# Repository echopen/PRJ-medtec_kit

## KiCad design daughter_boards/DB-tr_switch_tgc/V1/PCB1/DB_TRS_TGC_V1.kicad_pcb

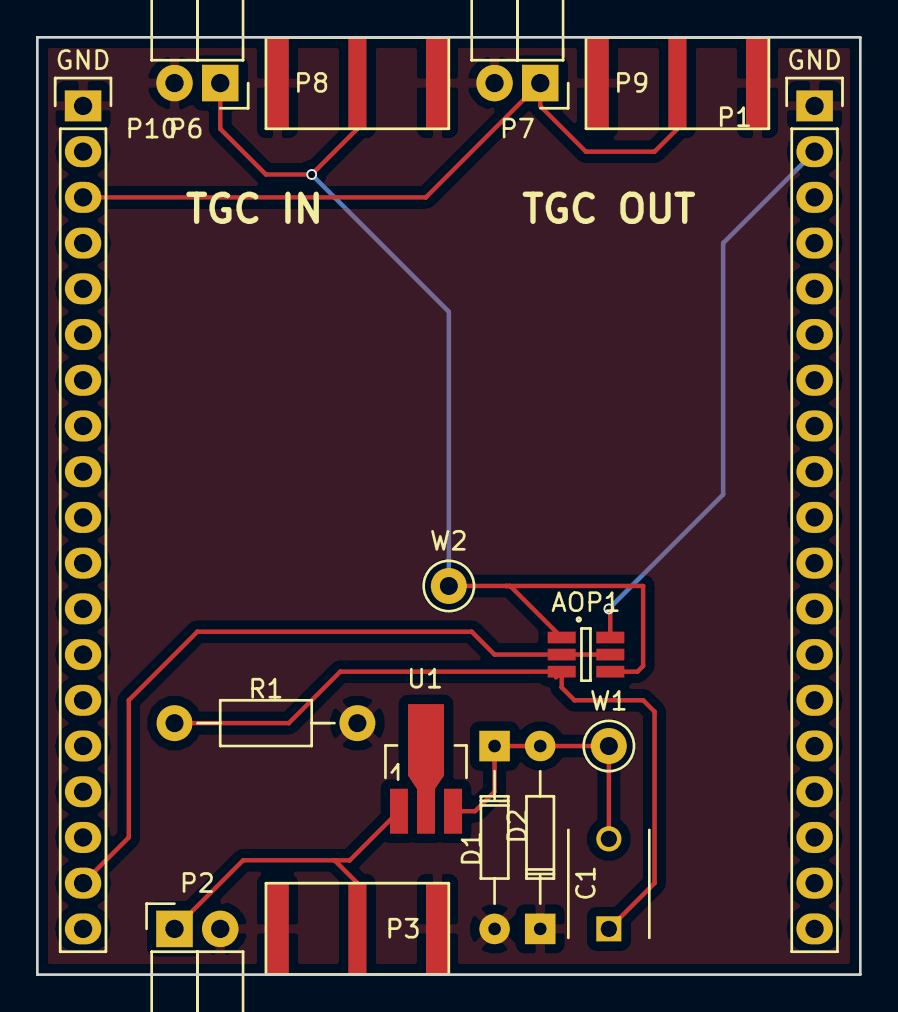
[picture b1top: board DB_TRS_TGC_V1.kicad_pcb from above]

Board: 2 copper layers, 45.7 x 52.1 mm, 16 parts (0 on the bottom side), 8 nets.

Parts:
AOP1: OPA625; SOT-23-6_Handsoldering(OPA625)
C1: 1n; C_TH_common
D1: 1N4148; D_TH_common
D2: IN4148; D_TH_common
P1, P10: CONN_01X19; Header_pin_1x19
P2, P6, P7: CONN_01X02; Socket_Strip_Angled_1x02
P3, P8, P9: SMA
R1: 220; Resistor_TH_common
U1: MD0100; SOT89-3_(MD0100)
W1, W2: TEST_1P; Test_Point_Keystone_5000-5004_Miniature

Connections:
GND: D1.2, D2.1, P1.1, P2.2, P3.2, P6.2, P7.2, P8.2, P9.2, P10.1, R1.2
unnamed: AOP1.1, AOP1.4, P6.1, P8.1, W2.1
unnamed: AOP1.2, AOP1.5, P10.18
unnamed: AOP1.3, C1.1, R1.1
unnamed: AOP1.6, P1.2
unnamed: C1.2, D1.1, D2.2, U1.3, W1.1
unnamed: P2.1, P3.1, U1.1
unnamed: P7.1, P9.1, P10.3

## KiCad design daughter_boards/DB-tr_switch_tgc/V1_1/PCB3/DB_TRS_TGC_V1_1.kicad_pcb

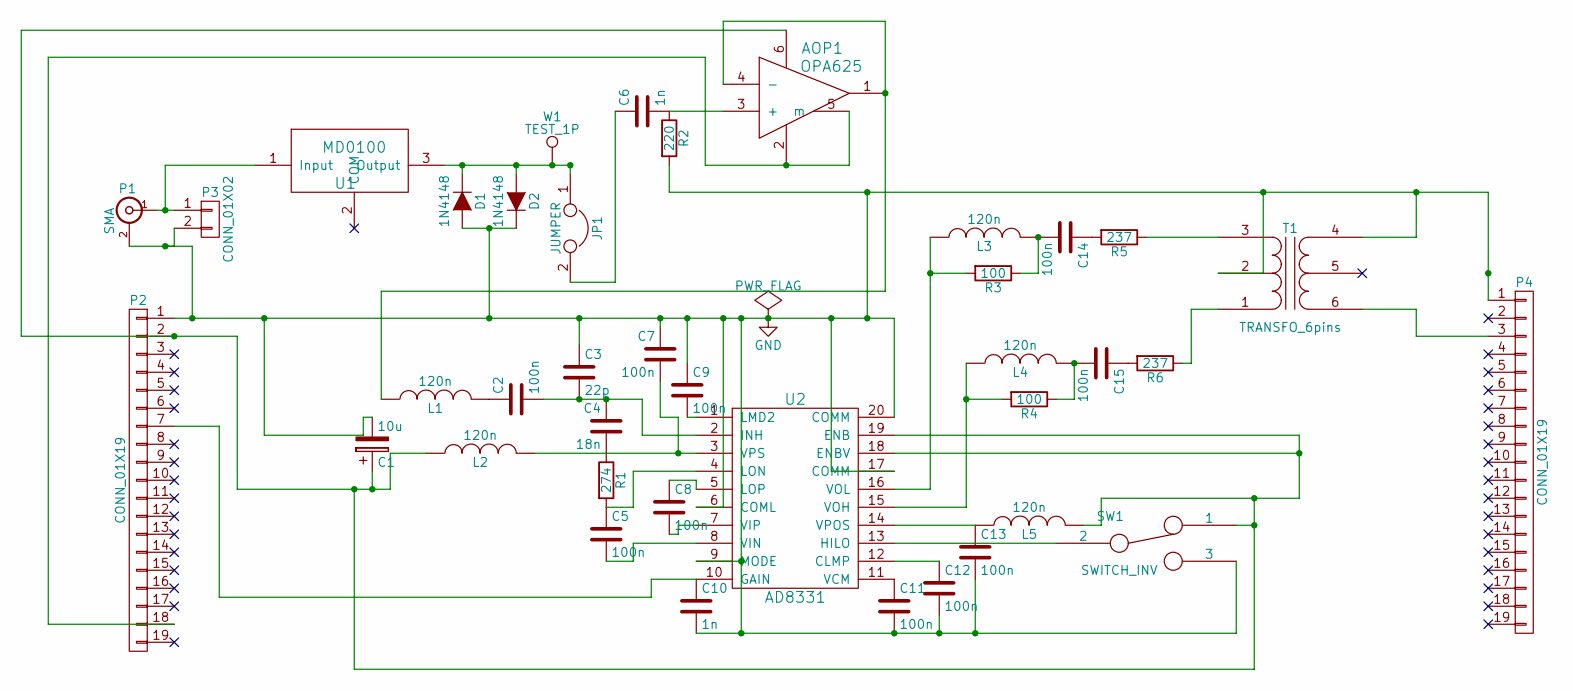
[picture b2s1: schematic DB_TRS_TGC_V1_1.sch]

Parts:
AOP1: OPA625; SOT-23-6_Handsoldering(OPA625)
C1: 10u; CP_TH_common
C2, C5, C7, C8, C9, C11, C12, C13, C14, C15: 100n; C_TH_common
C3: 22p; C_TH_common
C4: 18n; C_TH_common
C6, C10: 1n; C_TH_common
D1, D2: 1N4148; D_TH_common
JP1: JUMPER; Jumper
L1, L2, L3, L4, L5: 120n; INDUCTOR_TH_common
P1: SMA
P2, P4: CONN_01X19; Header_1x19
P3: CONN_01X02; Socket_Strip_Angled_1x02
R1: 274; Resistor_TH_common
R2: 220; Resistor_TH_common
R3, R4: 100; Resistor_TH_common
R5, R6: 237; Resistor_TH_common
SW1: SWITCH_INV; SW_Micro_SPST
T1: TRANSFO_6pins; Transfo_6pins
U1: MD0100; SOT89-3_Housing_Handsoldering
U2: AD8331; SSOP-20_5.3x7.2mm_Pitch0.65mm
W1: TEST_1P; Test_Point_Keystone_5000-5004_Miniature

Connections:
GND: C1.2, C3.1, C7.1, C9.1, C10.2, C11.2, C12.2, C13.2, D1.2 (A), D2.1 (K), P1.2 (Ext), P2.1, P3.2, P4.1, R2.2, SW1.3, T1.2 (PM), T1.4 (S2), U2.6 (COML), U2.9 (MODE), U2.17 (COMM), U2.20 (COMM)
unnamed: AOP1.1, AOP1.4 (-), L1.1
unnamed: AOP1.2, AOP1.5 (m), P2.18
unnamed: AOP1.3 (+), C6.2, R2.1
unnamed: AOP1.6, C1.1, L2.1, L5.2, P2.2, SW1.1, U2.18 (ENBV), U2.19 (ENB)
unnamed: C2.1, L1.2
unnamed: C2.2, C3.2, C4.1, U2.2 (INH)
unnamed: C4.2, R1.1
unnamed: C5.1, R1.2, U2.4 (LON)
unnamed: C5.2, U2.8 (VIN)
unnamed: C6.1, JP1.2
unnamed: C7.2, L2.2, U2.3 (VPS)
unnamed: C8.1, U2.5 (LOP)
unnamed: C8.2, U2.7 (VIP)
unnamed: C9.2, U2.1 (LMD2)
unnamed: C10.1, P2.7, U2.10 (GAIN)
unnamed: C11.1, U2.11 (VCM)
unnamed: C12.1, U2.12 (CLMP)
unnamed: C13.1, L5.1, U2.14 (VPOS)
unnamed: C14.1, R5.2
unnamed: C14.2, L3.2, R3.1
unnamed: C15.1, R6.2
unnamed: C15.2, L4.2, R4.1
unnamed: D1.1 (K), D2.2 (A), JP1.1, U1.3 (Output), W1.1
unnamed: L3.1, R3.2, U2.16 (VOL)
unnamed: L4.1, R4.2, U2.15 (VOH)
unnamed: P1.1 (In), P3.1, U1.1 (Input)
unnamed: P4.3, T1.6 (S1)
unnamed: R5.1, T1.3 (PR1)
unnamed: R6.1, T1.1 (PR2)
unnamed: SW1.2, U2.13 (HILO)

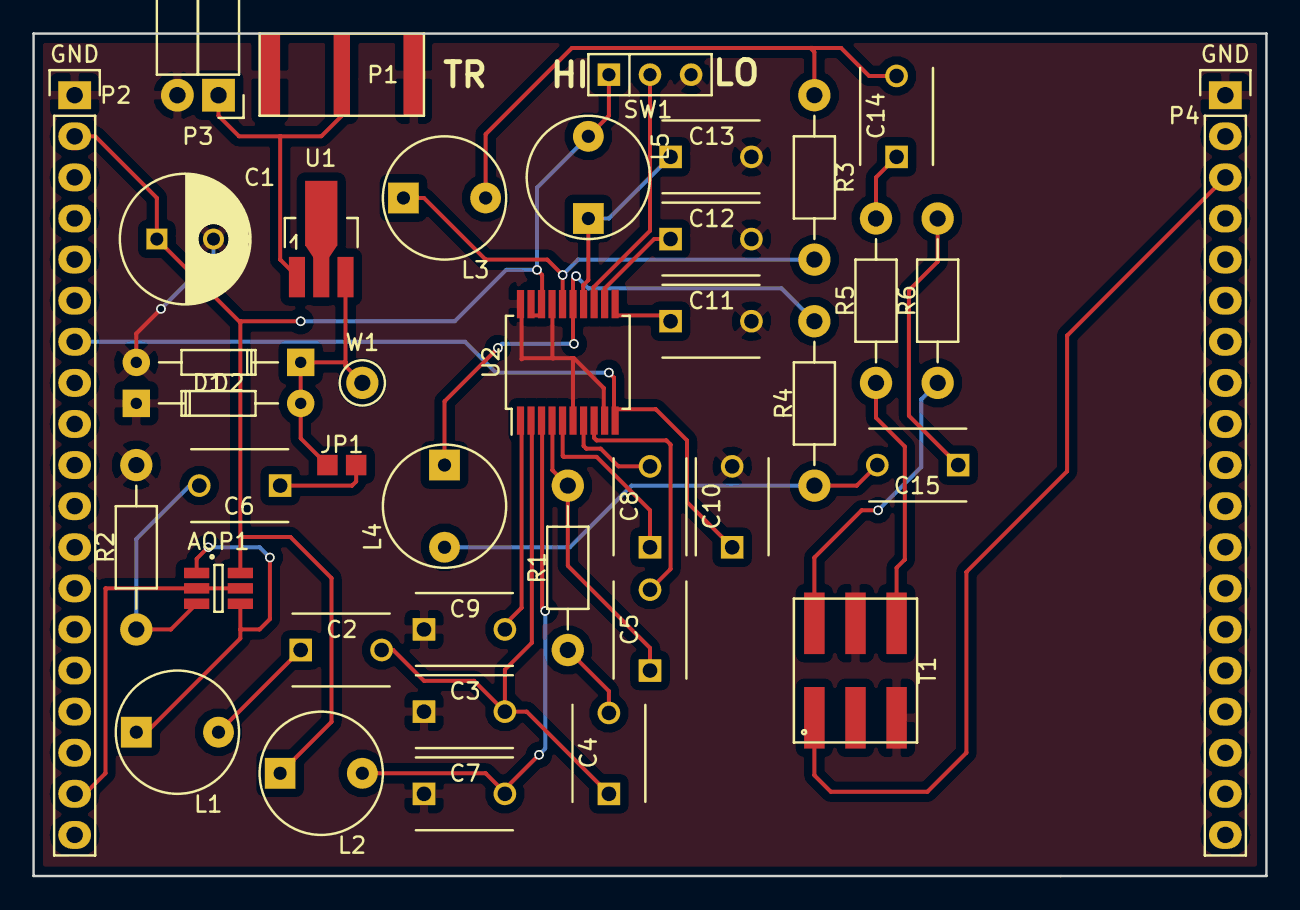
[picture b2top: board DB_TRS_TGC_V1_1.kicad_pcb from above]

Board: 2 copper layers, 76.2 x 52.1 mm, 39 parts (0 on the bottom side), 31 nets.

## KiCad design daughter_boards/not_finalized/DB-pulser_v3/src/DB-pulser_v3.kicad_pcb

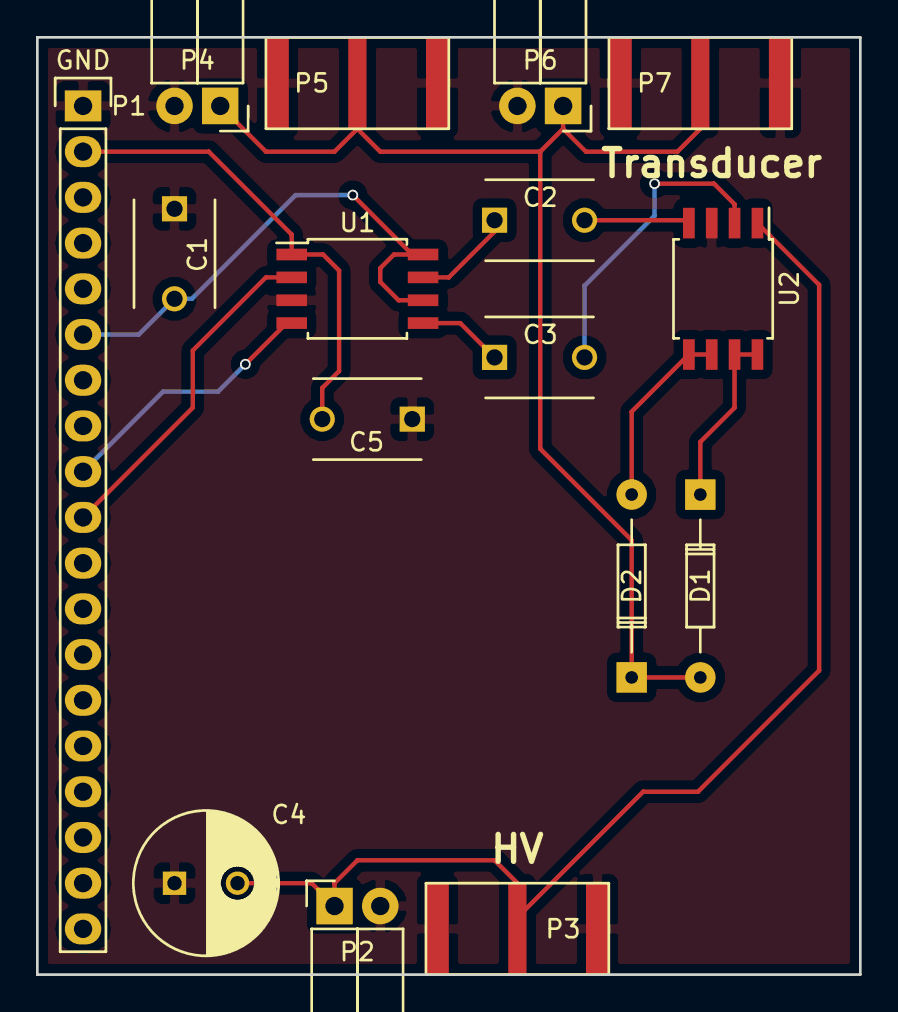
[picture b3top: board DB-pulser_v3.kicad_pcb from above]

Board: 2 copper layers, 45.7 x 52.1 mm, 16 parts (0 on the bottom side), 13 nets.

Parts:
C1: 470n; C_TH_common
C2, C3: 10n; C_TH_common
C4: 33u (150V); CP_TH_common
C5: 1u; C_TH_common
D1, D2: 1N4148; D_TH_common
P1: CONN_01X19; Header_pin_angled_1x19
P2, P4, P6: CONN_01X02; Socket_Strip_Angled_1x02
P3, P5, P7: SMA
U1: MD1211; SOIJ-8_5.3x5.3mm_Pitch1.27mm
U2: TC6320; SOIJ-8_5.3x5.3mm_Pitch1.27mm

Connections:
GND: C1.1, C4.1, C5.1, P1.1, P2.2, P3.2, P4.2, P5.2, P6.2, P7.2, U1.3, U2.3
unnamed: C1.2, P1.6, U1.6, U1.8
unnamed: C2.1, U1.7
unnamed: C2.2, U2.4
unnamed: C3.1, U1.5
unnamed: C3.2, U2.2
unnamed: C4.2, P2.1, P3.1, U2.1
unnamed: C5.2, P1.2, U1.1
unnamed: D1.1, U2.7, U2.8
unnamed: D1.2, D2.1, P4.1, P5.1, P6.1, P7.1
unnamed: D2.2, U2.5, U2.6
unnamed: P1.9, U1.4
unnamed: P1.10, U1.2

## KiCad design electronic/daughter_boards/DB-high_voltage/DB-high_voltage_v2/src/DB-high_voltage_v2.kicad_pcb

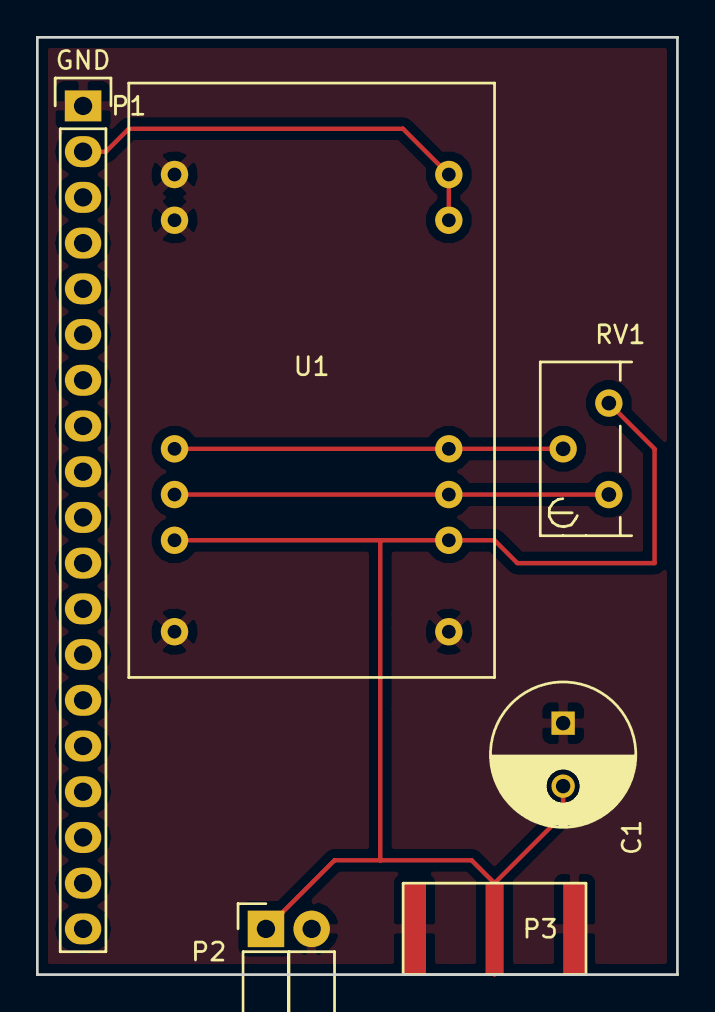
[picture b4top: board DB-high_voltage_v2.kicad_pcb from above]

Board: 2 copper layers, 35.6 x 52.1 mm, 6 parts (0 on the bottom side), 5 nets.

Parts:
C1: 4.7u (150V); CP_TH_common
P1: CONN_01X19; Header_pin_angled_1x19
P2: CONN_01X02; Socket_Strip_Angled_1x02
P3: SMA
RV1: POT; Potentiometer_Bourns_3296Y_3-8Zoll_Angular_ScrewUp
U1: R05-100B; RECOM

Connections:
GND: C1.1, P1.1, P2.2, P3.2, U1.2, U1.3, U1.12, U1.13
unnamed: C1.2, P2.1, P3.1, RV1.3, U1.10, U1.15
unnamed: P1.2, U1.22, U1.23
unnamed: RV1.1, U1.9, U1.16
unnamed: RV1.2, U1.8, U1.17

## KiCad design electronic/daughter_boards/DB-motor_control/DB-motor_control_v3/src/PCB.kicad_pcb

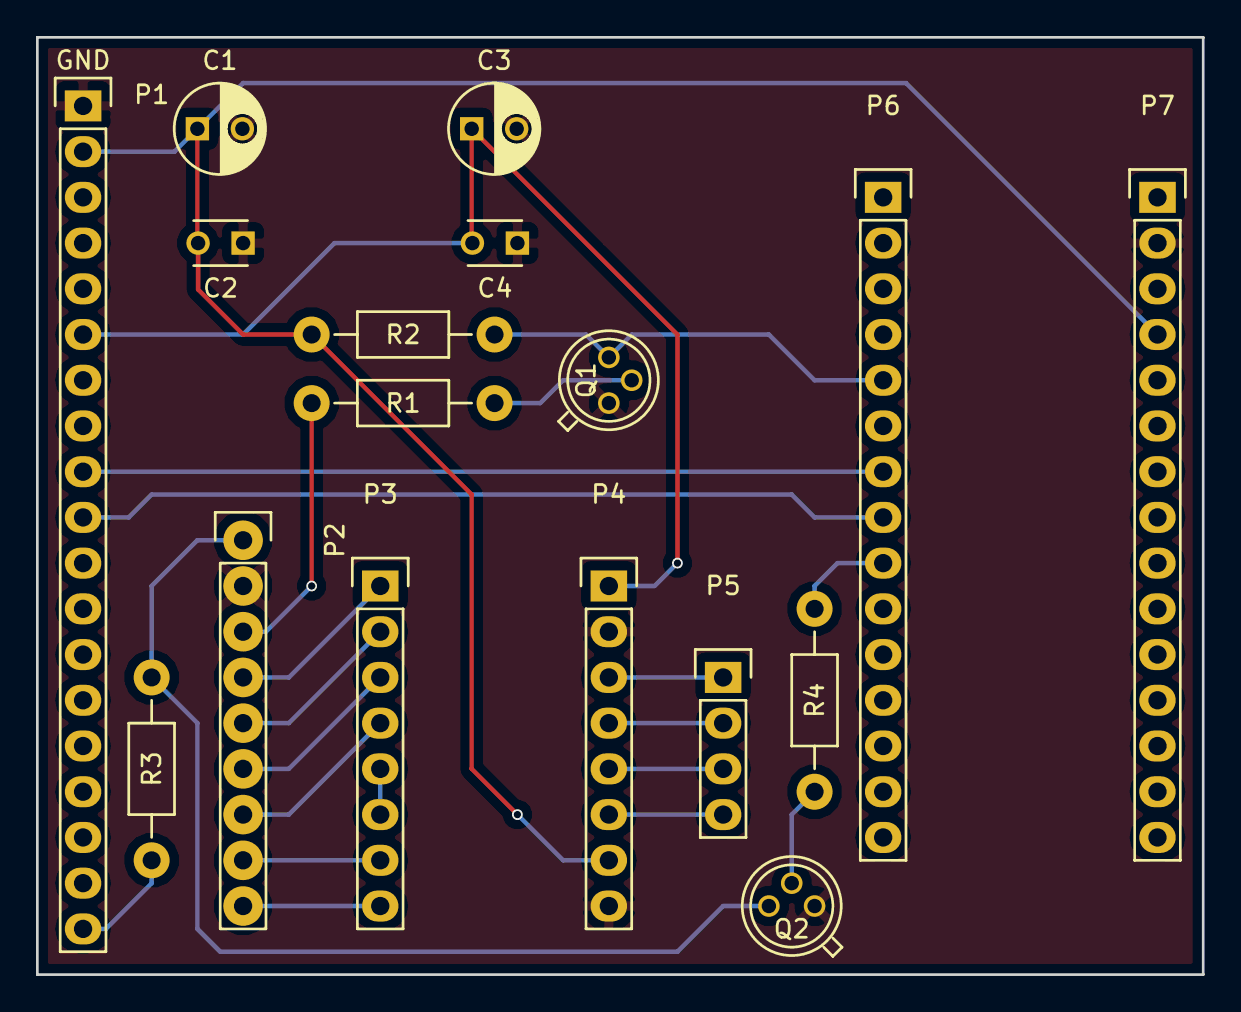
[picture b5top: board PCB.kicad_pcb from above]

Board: 2 copper layers, 64.8 x 52.1 mm, 17 parts (0 on the bottom side), 23 nets.

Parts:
C1: 10u; CP_small_TH_echopen
C2, C4: 100n; C_small_TH_echopen
C3: 100u; CP_small_TH_echopen
P1: CONN_01X19; Header_pin_angled_1x19
P2: CONN_01X09; Socket_1x09
P3, P4: CONN_01X08; Pin_Header_Straight_1x08
P5: CONN_01X04; Pin_Header_Straight_1x04
P6, P7: CONN_01X15; Pin_Header_Straight_1x15
Q1, Q2: 2N2222; TO-18_TH_common
R1, R4: 680; Resistor_TH_common
R2, R3: 1.5k; Resistor_TH_common

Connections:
GND: C1.2, C2.1, C3.2, C4.1, P1.1, P2.2, P4.2, P4.8, P7.2, Q1.1, Q2.1
unnamed: C1.1, C2.2, P1.2, P4.7, P7.4, R2.2
unnamed: C3.1, C4.2, P1.6, P4.1
unnamed: P1.9, P6.7
unnamed: P1.10, P6.8
unnamed: P1.19, R3.2
unnamed: P2.1, Q2.3, R3.1
unnamed: P2.3, R1.2
unnamed: P2.4, P3.1
unnamed: P2.5, P3.2
unnamed: P2.6, P3.3
unnamed: P2.7, P3.4
unnamed: P2.8, P3.7
unnamed: P2.9, P3.8
unnamed: P3.5, P3.6
unnamed: P4.3, P5.1
unnamed: P4.4, P5.2
unnamed: P4.5, P5.3
unnamed: P4.6, P5.4
unnamed: P6.5, Q1.3, R2.1
unnamed: P6.9, R4.1
unnamed: Q1.2, R1.1
unnamed: Q2.2, R4.2
